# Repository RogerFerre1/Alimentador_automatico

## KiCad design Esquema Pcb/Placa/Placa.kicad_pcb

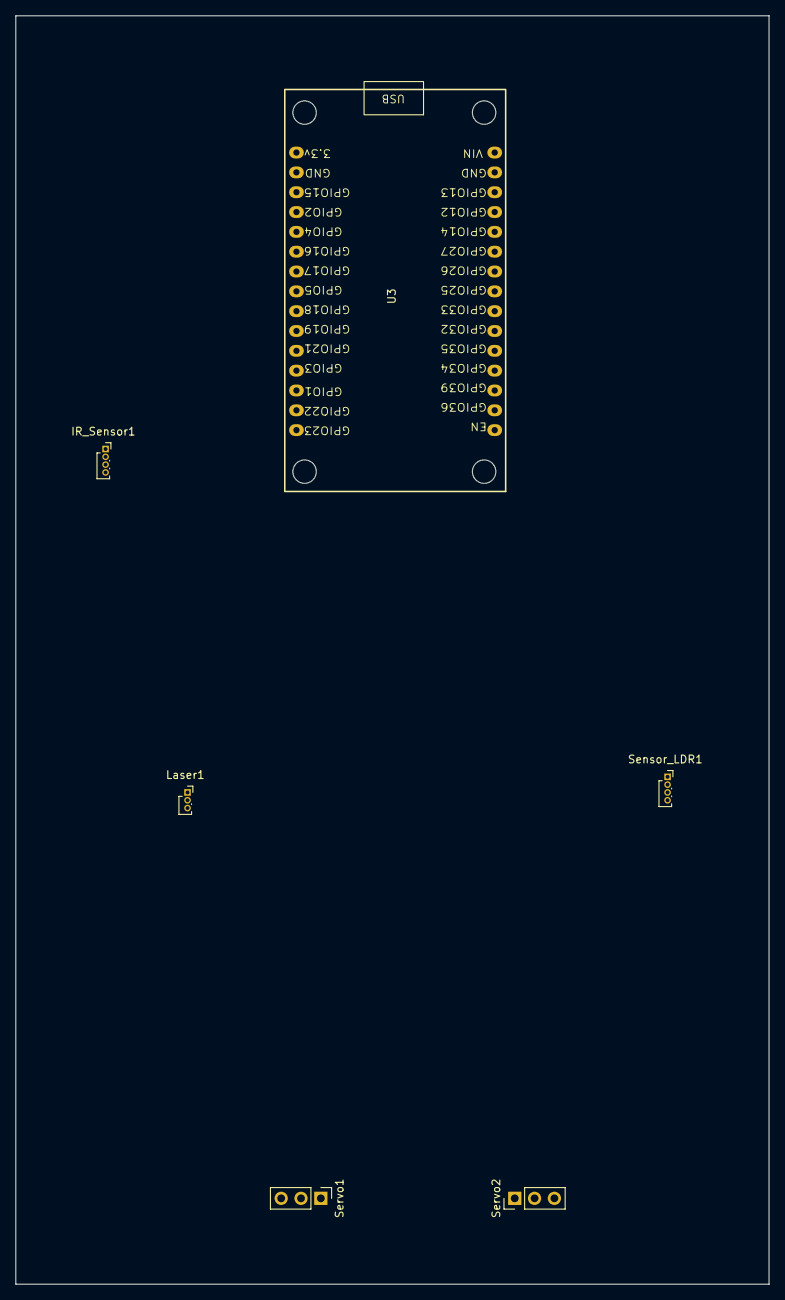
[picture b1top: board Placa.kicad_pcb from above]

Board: 2 copper layers, 96.5 x 162.5 mm, 6 parts (0 on the bottom side), 5 nets, no tracks yet.

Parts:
IR_Sensor1: Conn_01x04_Socket; PinSocket_1x04_P1.00mm_Vertical
Laser1: Conn_01x03_Socket; PinSocket_1x03_P1.00mm_Vertical
Sensor_LDR1: Conn_01x04_Socket; PinSocket_1x04_P1.00mm_Vertical
Servo1, Servo2: Motor_Servo; PinHeader_1x03_P2.54mm_Vertical
U3: ESP32-WROOM-32; ESP32_30pin

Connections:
+5V: IR_Sensor1.1 (VCC), Laser1.2 (VCC), Laser1.3 (Signal), Sensor_LDR1.4 (VCC), Servo1.2 (+), Servo2.2 (+), U3.2 (VDD)
GND: IR_Sensor1.2 (GND), Laser1.1 (GND), Sensor_LDR1.3 (GND), Servo1.3 (-), Servo2.3 (-), U3.1 (GND), U3.15 (GND)
unnamed: Sensor_LDR1.2 (DO), U3.14 (IO12)
unnamed: Servo1.1 (PWM), U3.13 (IO14)
unnamed: Servo2.1 (PWM), U3.12 (IO27)
